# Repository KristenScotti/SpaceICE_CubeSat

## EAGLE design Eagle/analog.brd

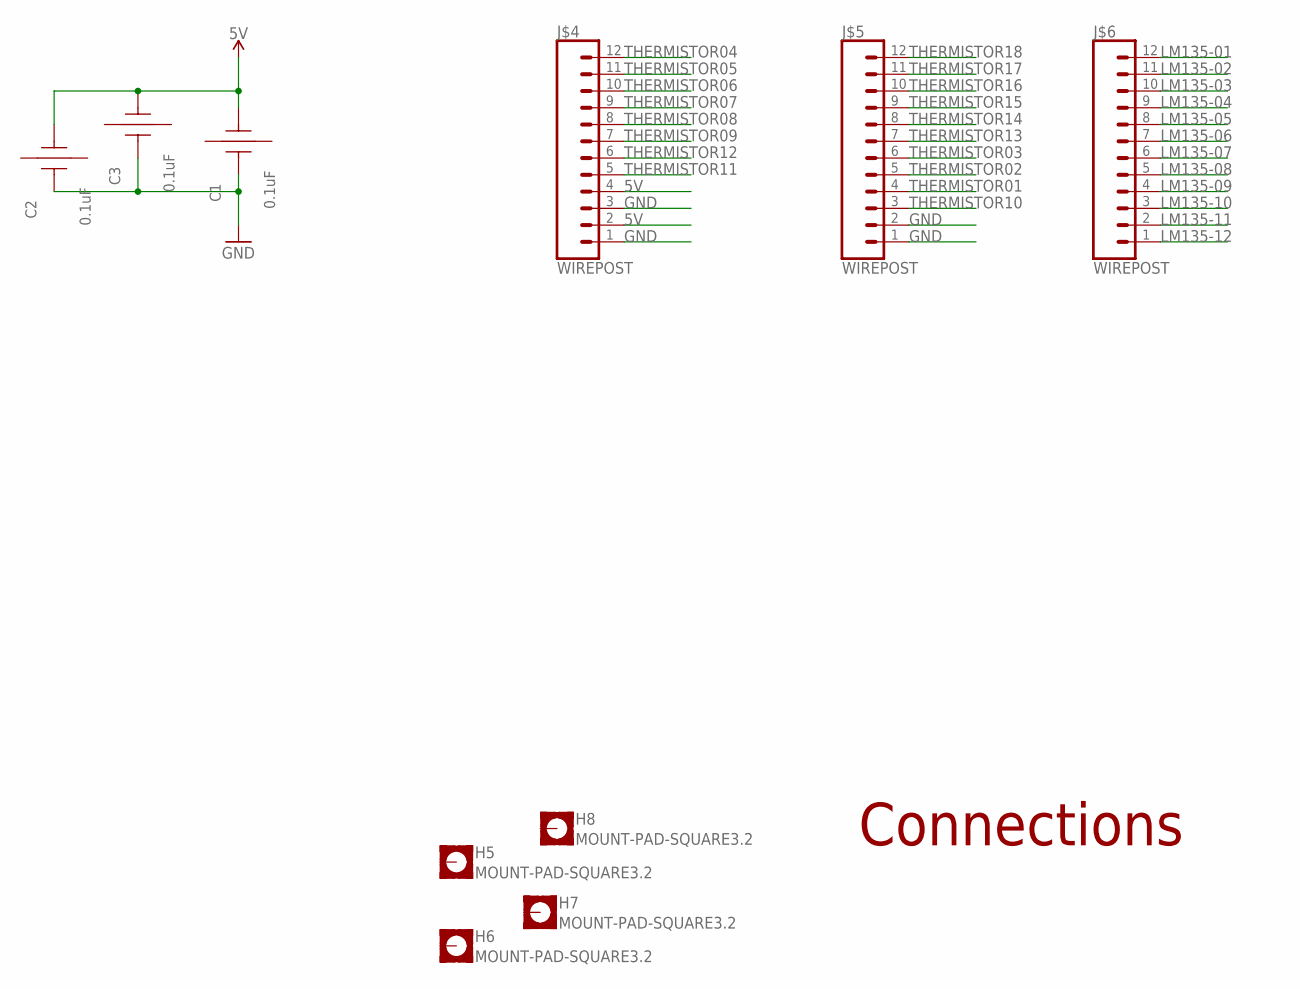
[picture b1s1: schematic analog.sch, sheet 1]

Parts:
C1, C2, C3: 0.1uF; X14
H5, H6, H7, H8: MOUNT-PAD-SQUARE3.2; 3,2-PAD-SQUARE
J$4, J$5, J$6: WIREPOST; WIREWRAPPOST

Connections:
5V: C1.2 (22), C2.2 (22), C3.2 (22), J$4.2, J$4.4; also elsewhere on the board
GND: C1.1 (11), C2.1 (11), C3.1 (11), J$4.1, J$4.3, J$5.1, J$5.2; also elsewhere on the board
LM135-01: J$6.12; also elsewhere on the board
LM135-02: J$6.11; also elsewhere on the board
LM135-03: J$6.10; also elsewhere on the board
LM135-04: J$6.9; also elsewhere on the board
LM135-05: J$6.8; also elsewhere on the board
LM135-06: J$6.7; also elsewhere on the board
LM135-07: J$6.6; also elsewhere on the board
LM135-08: J$6.5; also elsewhere on the board
LM135-09: J$6.4; also elsewhere on the board
LM135-10: J$6.3; also elsewhere on the board
LM135-11: J$6.2; also elsewhere on the board
LM135-12: J$6.1; also elsewhere on the board
THERMISTOR01: J$5.4; also elsewhere on the board
THERMISTOR02: J$5.5; also elsewhere on the board
THERMISTOR03: J$5.6; also elsewhere on the board
THERMISTOR04: J$4.12; also elsewhere on the board
THERMISTOR05: J$4.11; also elsewhere on the board
THERMISTOR06: J$4.10; also elsewhere on the board
THERMISTOR07: J$4.9; also elsewhere on the board
THERMISTOR08: J$4.8; also elsewhere on the board
THERMISTOR09: J$4.7; also elsewhere on the board
THERMISTOR10: J$5.3; also elsewhere on the board
THERMISTOR11: J$4.5; also elsewhere on the board
THERMISTOR12: J$4.6; also elsewhere on the board
THERMISTOR13: J$5.7; also elsewhere on the board
THERMISTOR14: J$5.8; also elsewhere on the board
THERMISTOR15: J$5.9; also elsewhere on the board
THERMISTOR16: J$5.10; also elsewhere on the board
THERMISTOR17: J$5.11; also elsewhere on the board
THERMISTOR18: J$5.12; also elsewhere on the board

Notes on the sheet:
Connections

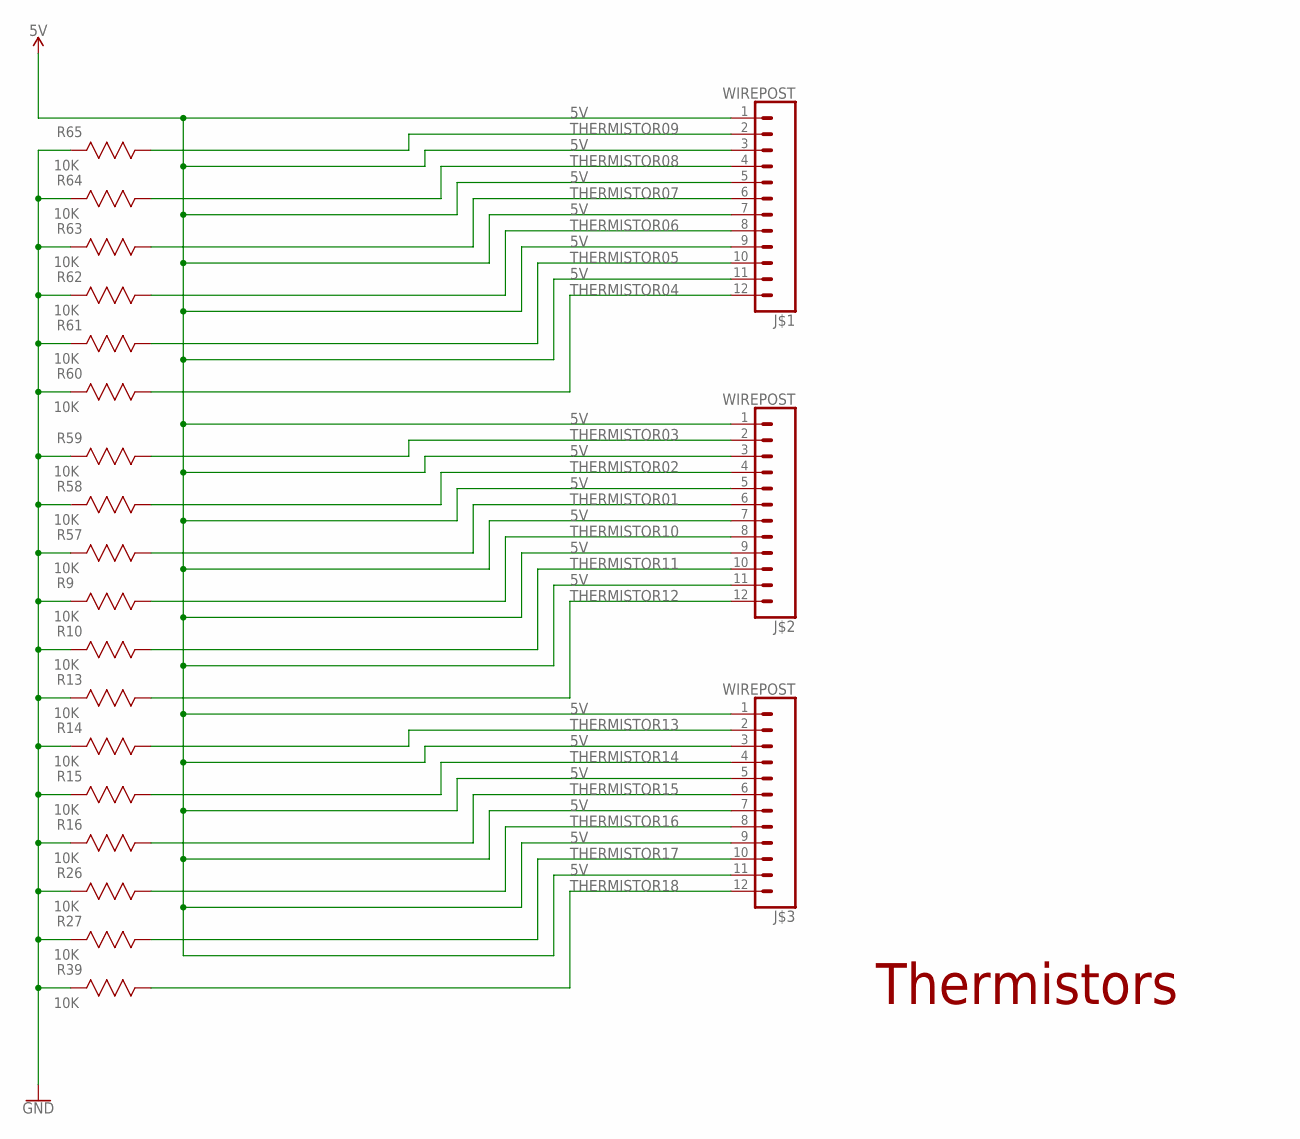
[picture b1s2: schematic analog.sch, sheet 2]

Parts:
J$1, J$2, J$3: WIREPOST; WIREWRAPPOST
R9, R10, R13, R14, R15, R16, R26, R27, R39, R57, R58, R59, R60, R61, R62, R63, R64, R65: 10K; RC0603N

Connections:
5V: J$1.1, J$1.3, J$1.5, J$1.7, J$1.9, J$1.11, J$2.1, J$2.3, J$2.5, J$2.7, J$2.9, J$2.11, J$3.1, J$3.3, J$3.5, J$3.7, J$3.9, J$3.11; also elsewhere on the board
GND: R9.2 (22), R10.2 (22), R13.2 (22), R14.2 (22), R15.2 (22), R16.2 (22), R26.2 (22), R27.2 (22), R39.2 (22), R57.2 (22), R58.2 (22), R59.2 (22), R60.2 (22), R61.2 (22), R62.2 (22), R63.2 (22), R64.2 (22), R65.2 (22); also elsewhere on the board
THERMISTOR01: J$2.6, R57.1 (11); also elsewhere on the board
THERMISTOR02: J$2.4, R58.1 (11); also elsewhere on the board
THERMISTOR03: J$2.2, R59.1 (11); also elsewhere on the board
THERMISTOR04: J$1.12, R60.1 (11); also elsewhere on the board
THERMISTOR05: J$1.10, R61.1 (11); also elsewhere on the board
THERMISTOR06: J$1.8, R62.1 (11); also elsewhere on the board
THERMISTOR07: J$1.6, R63.1 (11); also elsewhere on the board
THERMISTOR08: J$1.4, R64.1 (11); also elsewhere on the board
THERMISTOR09: J$1.2, R65.1 (11); also elsewhere on the board
THERMISTOR10: J$2.8, R9.1 (11); also elsewhere on the board
THERMISTOR11: J$2.10, R10.1 (11); also elsewhere on the board
THERMISTOR12: J$2.12, R13.1 (11); also elsewhere on the board
THERMISTOR13: J$3.2, R14.1 (11); also elsewhere on the board
THERMISTOR14: J$3.4, R15.1 (11); also elsewhere on the board
THERMISTOR15: J$3.6, R16.1 (11); also elsewhere on the board
THERMISTOR16: J$3.8, R26.1 (11); also elsewhere on the board
THERMISTOR17: J$3.10, R27.1 (11); also elsewhere on the board
THERMISTOR18: J$3.12, R39.1 (11); also elsewhere on the board

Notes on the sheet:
Thermistors

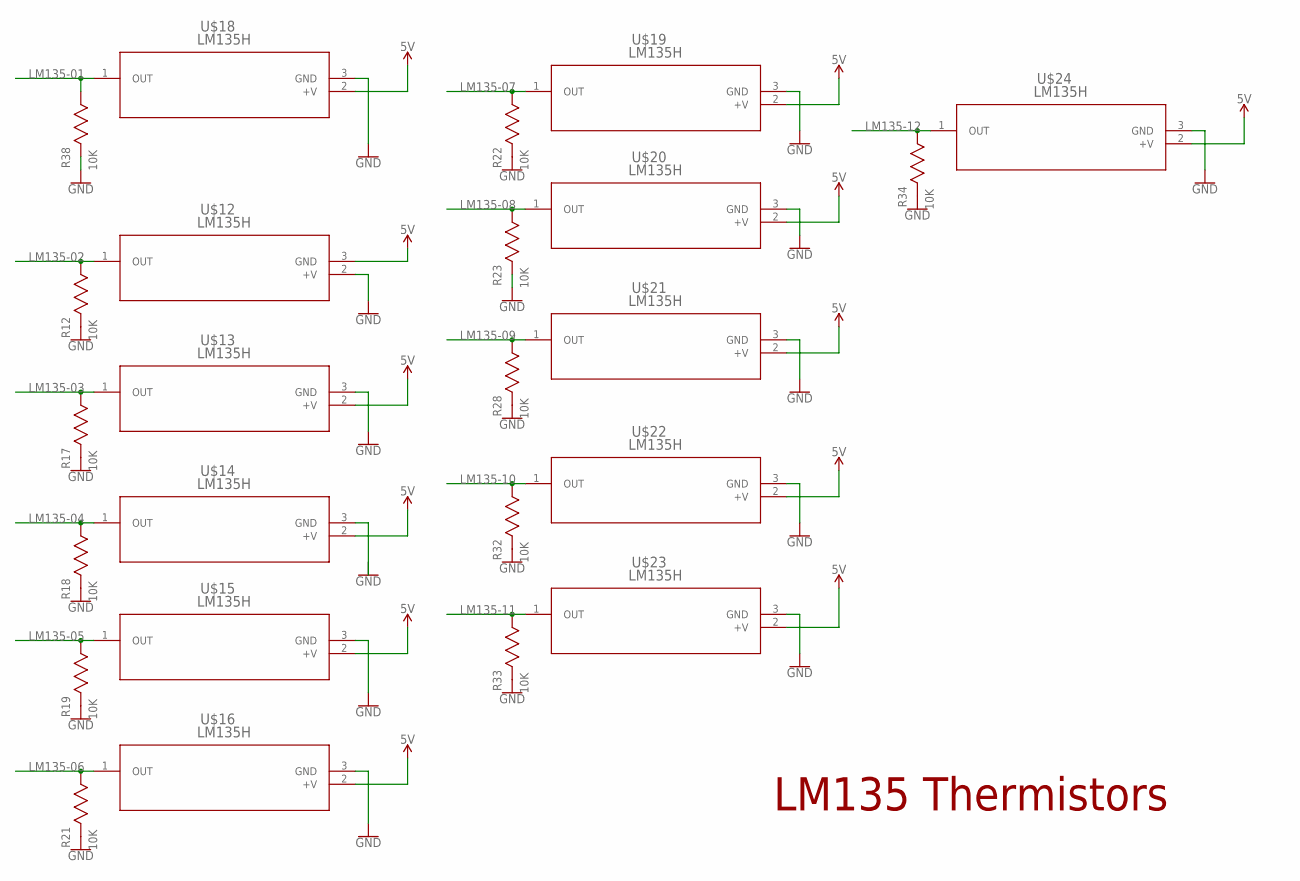
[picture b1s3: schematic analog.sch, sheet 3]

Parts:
R12, R17, R18, R19, R21, R22, R23, R28, R32, R33, R34, R38: 10K; RC0603N
U$12, U$13, U$14, U$15, U$16, U$18, U$19, U$20, U$21, U$22, U$23, U$24: LM135H; TO46

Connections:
5V: U$12.3 (GND), U$13.2 (+V), U$14.2 (+V), U$15.2 (+V), U$16.2 (+V), U$18.2 (+V), U$19.2 (+V), U$20.2 (+V), U$21.2 (+V), U$22.2 (+V), U$23.2 (+V), U$24.2 (+V); also elsewhere on the board
GND: R12.2 (22), R17.2 (22), R18.2 (22), R19.2 (22), R21.2 (22), R22.2 (22), R23.2 (22), R28.2 (22), R32.2 (22), R33.2 (22), R34.2 (22), R38.2 (22), U$12.2 (+V), U$13.3 (GND), U$14.3 (GND), U$15.3 (GND), U$16.3 (GND), U$18.3 (GND), U$19.3 (GND), U$20.3 (GND), U$21.3 (GND), U$22.3 (GND), U$23.3 (GND), U$24.3 (GND); also elsewhere on the board
LM135-01: R38.1 (11), U$18.1 (OUT); also elsewhere on the board
LM135-02: R12.1 (11), U$12.1 (OUT); also elsewhere on the board
LM135-03: R17.1 (11), U$13.1 (OUT); also elsewhere on the board
LM135-04: R18.1 (11), U$14.1 (OUT); also elsewhere on the board
LM135-05: R19.1 (11), U$15.1 (OUT); also elsewhere on the board
LM135-06: R21.1 (11), U$16.1 (OUT); also elsewhere on the board
LM135-07: R22.1 (11), U$19.1 (OUT); also elsewhere on the board
LM135-08: R23.1 (11), U$20.1 (OUT); also elsewhere on the board
LM135-09: R28.1 (11), U$21.1 (OUT); also elsewhere on the board
LM135-10: R32.1 (11), U$22.1 (OUT); also elsewhere on the board
LM135-11: R33.1 (11), U$23.1 (OUT); also elsewhere on the board
LM135-12: R34.1 (11), U$24.1 (OUT); also elsewhere on the board

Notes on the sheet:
LM135 Thermistors

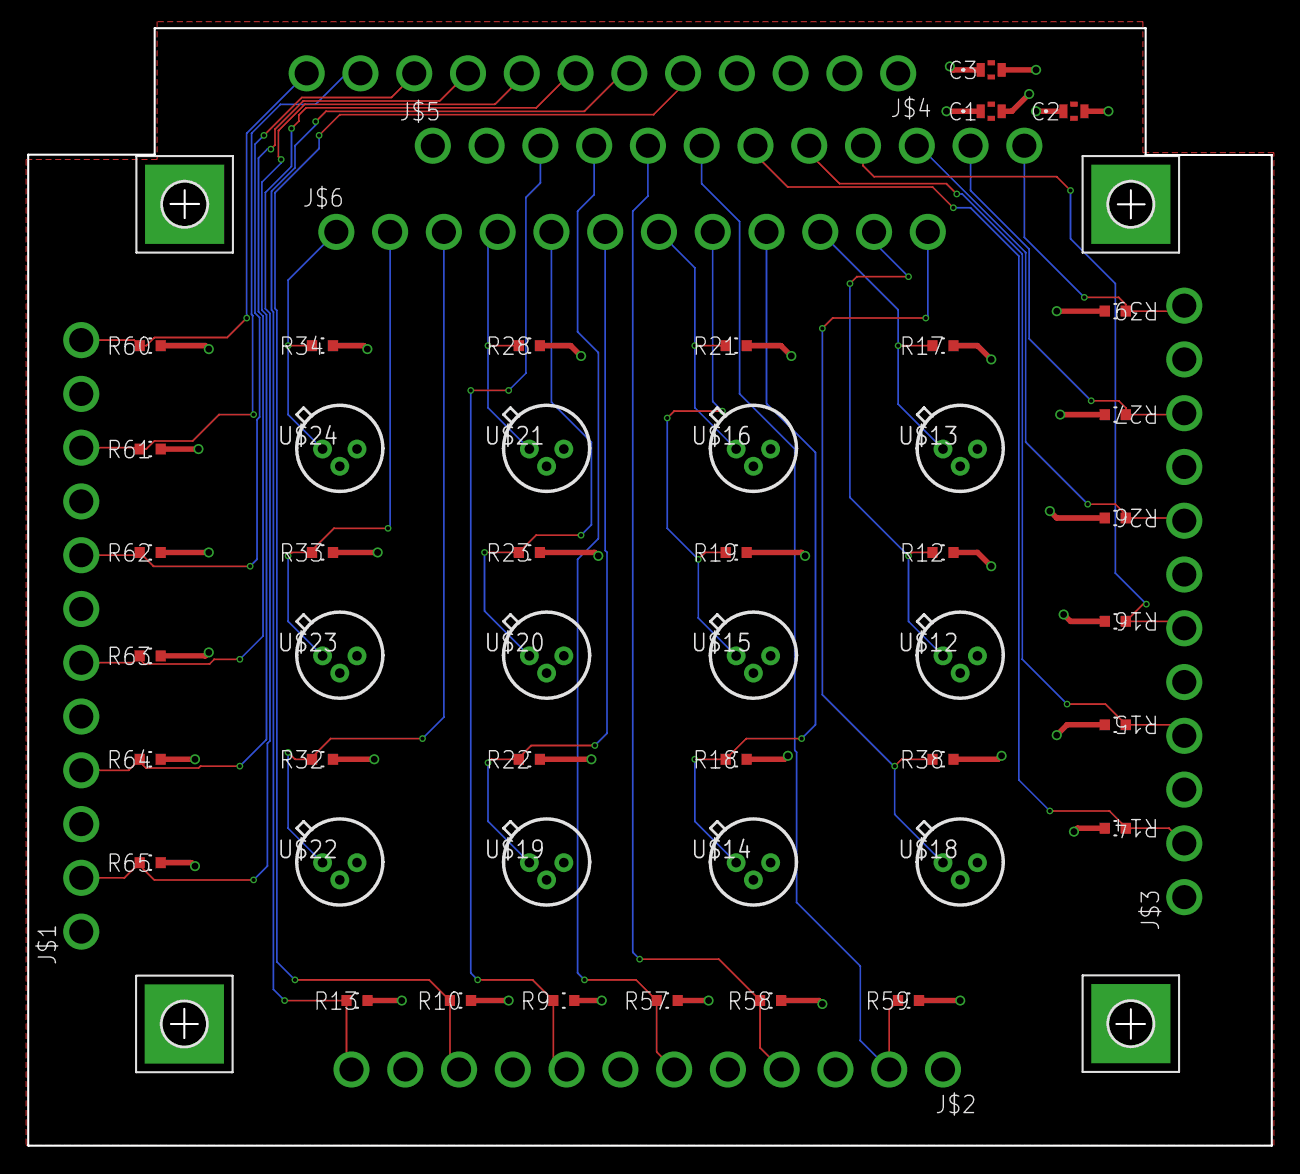
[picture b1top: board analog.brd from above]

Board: 4 copper layers, 91.6 x 82.3 mm, 55 parts (0 on the bottom side), 32 nets.

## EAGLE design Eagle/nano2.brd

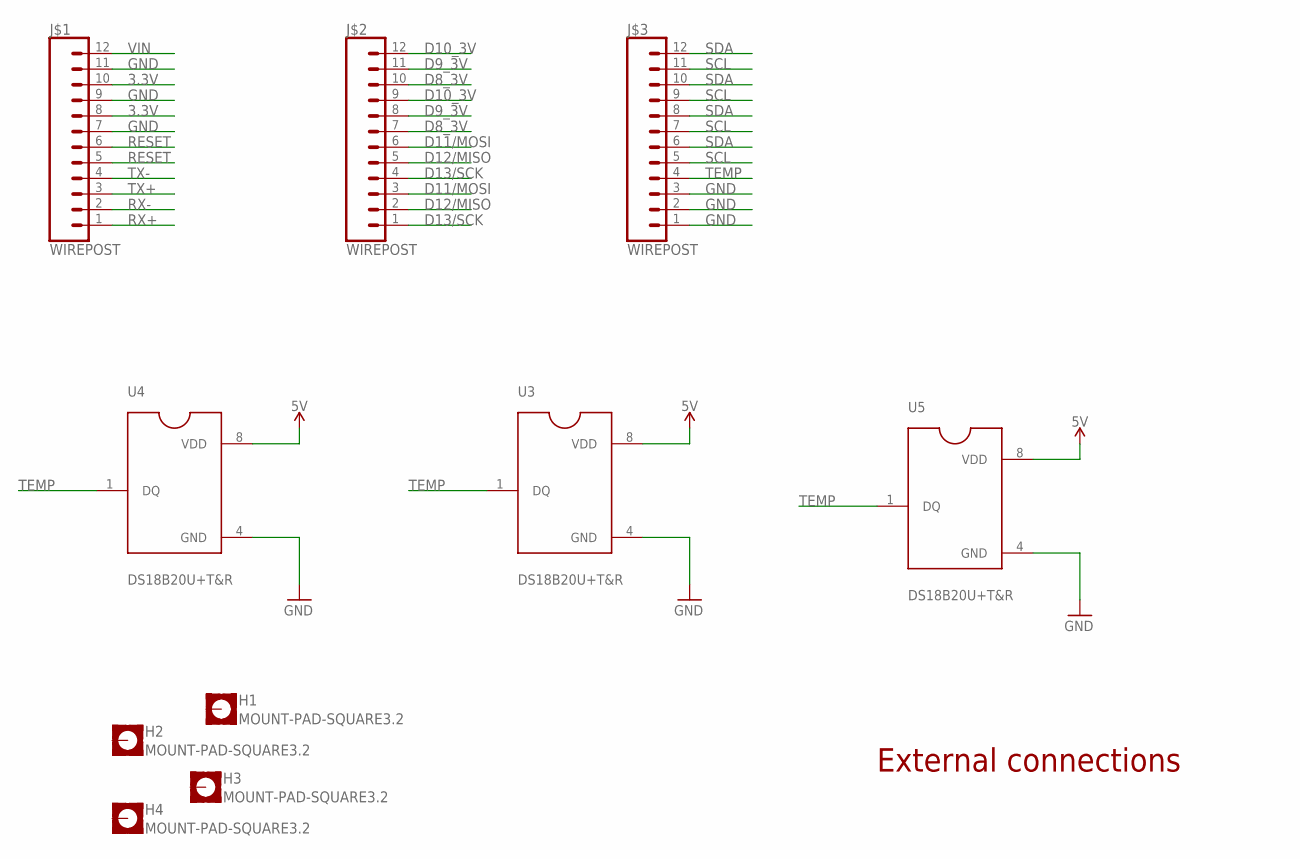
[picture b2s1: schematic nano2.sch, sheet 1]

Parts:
H1, H2, H3, H4: MOUNT-PAD-SQUARE3.2; 3,2-PAD-SQUARE
J$1, J$2, J$3: WIREPOST; WIREWRAPPOST
U3, U4, U5: DS18B20U+T&R; SOP65P500X110-8N

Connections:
3.3V: J$1.8, J$1.10; also elsewhere on the board
5V: U3.8 (VDD), U4.8 (VDD), U5.8 (VDD); also elsewhere on the board
D8_3V: J$2.7, J$2.10; also elsewhere on the board
D9_3V: J$2.8, J$2.11; also elsewhere on the board
D10_3V: J$2.9, J$2.12; also elsewhere on the board
D11/MOSI: J$2.3, J$2.6; also elsewhere on the board
D12/MISO: J$2.2, J$2.5; also elsewhere on the board
D13/SCK: J$2.1, J$2.4; also elsewhere on the board
GND: J$1.7, J$1.9, J$1.11, J$3.1, J$3.2, J$3.3, U3.4 (GND), U4.4 (GND), U5.4 (GND); also elsewhere on the board
RESET: J$1.5, J$1.6; also elsewhere on the board
RX+: J$1.1; also elsewhere on the board
RX-: J$1.2; also elsewhere on the board
SCL: J$3.5, J$3.7, J$3.9, J$3.11; also elsewhere on the board
SDA: J$3.6, J$3.8, J$3.10, J$3.12; also elsewhere on the board
TEMP: J$3.4, U3.1 (DQ), U4.1 (DQ), U5.1 (DQ)
TX+: J$1.3; also elsewhere on the board
TX-: J$1.4; also elsewhere on the board
VIN: J$1.12; also elsewhere on the board

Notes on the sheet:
External connections

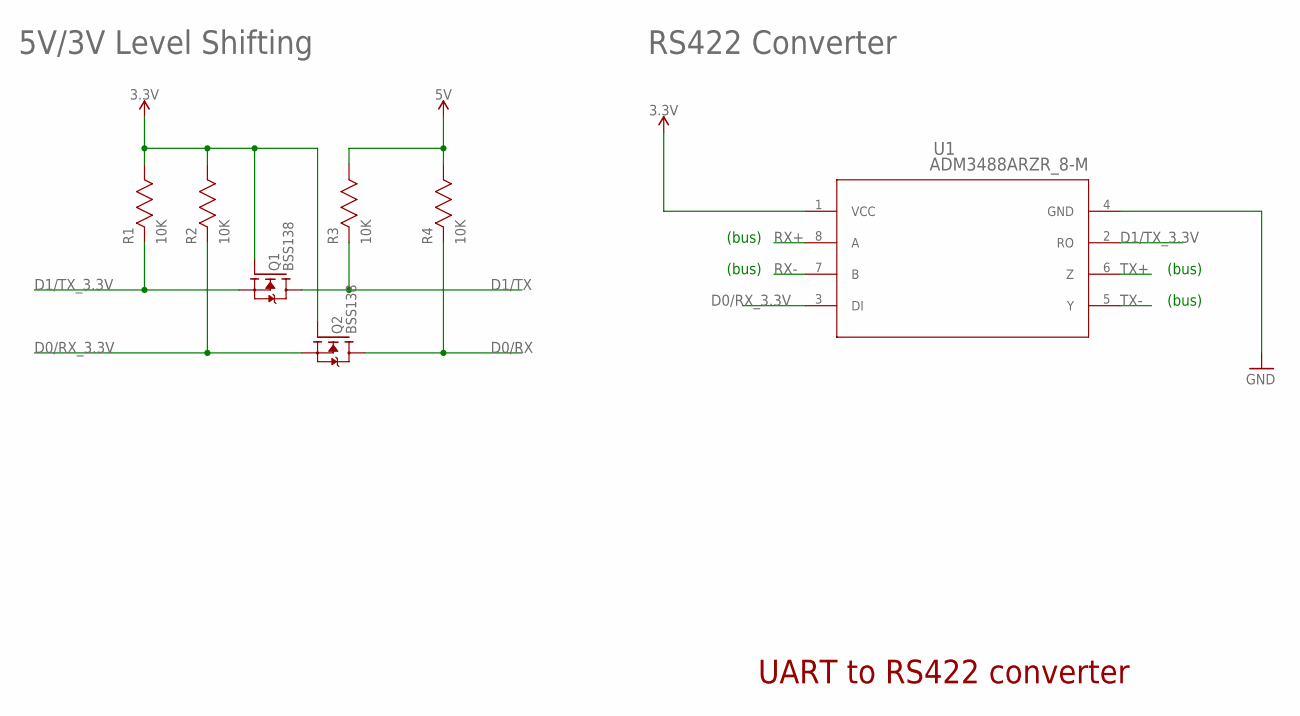
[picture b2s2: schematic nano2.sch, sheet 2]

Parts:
Q1, Q2: BSS138; SOT-23
R1, R2, R3, R4: 10K; RC0603N
U1: ADM3488ARZR_8-M; R_8-M

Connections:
3.3V: Q1.G, Q2.G, R1.1 (11), R2.1 (11), U1.1 (VCC); also elsewhere on the board
5V: R3.1 (11), R4.1 (11); also elsewhere on the board
D0/RX: Q2.D, R4.2 (22); also elsewhere on the board
D0/RX_3.3V: Q2.S, R2.2 (22), U1.3 (DI)
D1/TX: Q1.D, R3.2 (22); also elsewhere on the board
D1/TX_3.3V: Q1.S, R1.2 (22), U1.2 (RO)
GND: U1.4 (GND); also elsewhere on the board
RX+: U1.8 (A); also elsewhere on the board
RX-: U1.7 (B); also elsewhere on the board
TX+: U1.6 (Z); also elsewhere on the board
TX-: U1.5 (Y); also elsewhere on the board

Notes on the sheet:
5V/3V Level Shifting
UART to RS422 converter
(bus)
RS422 Converter

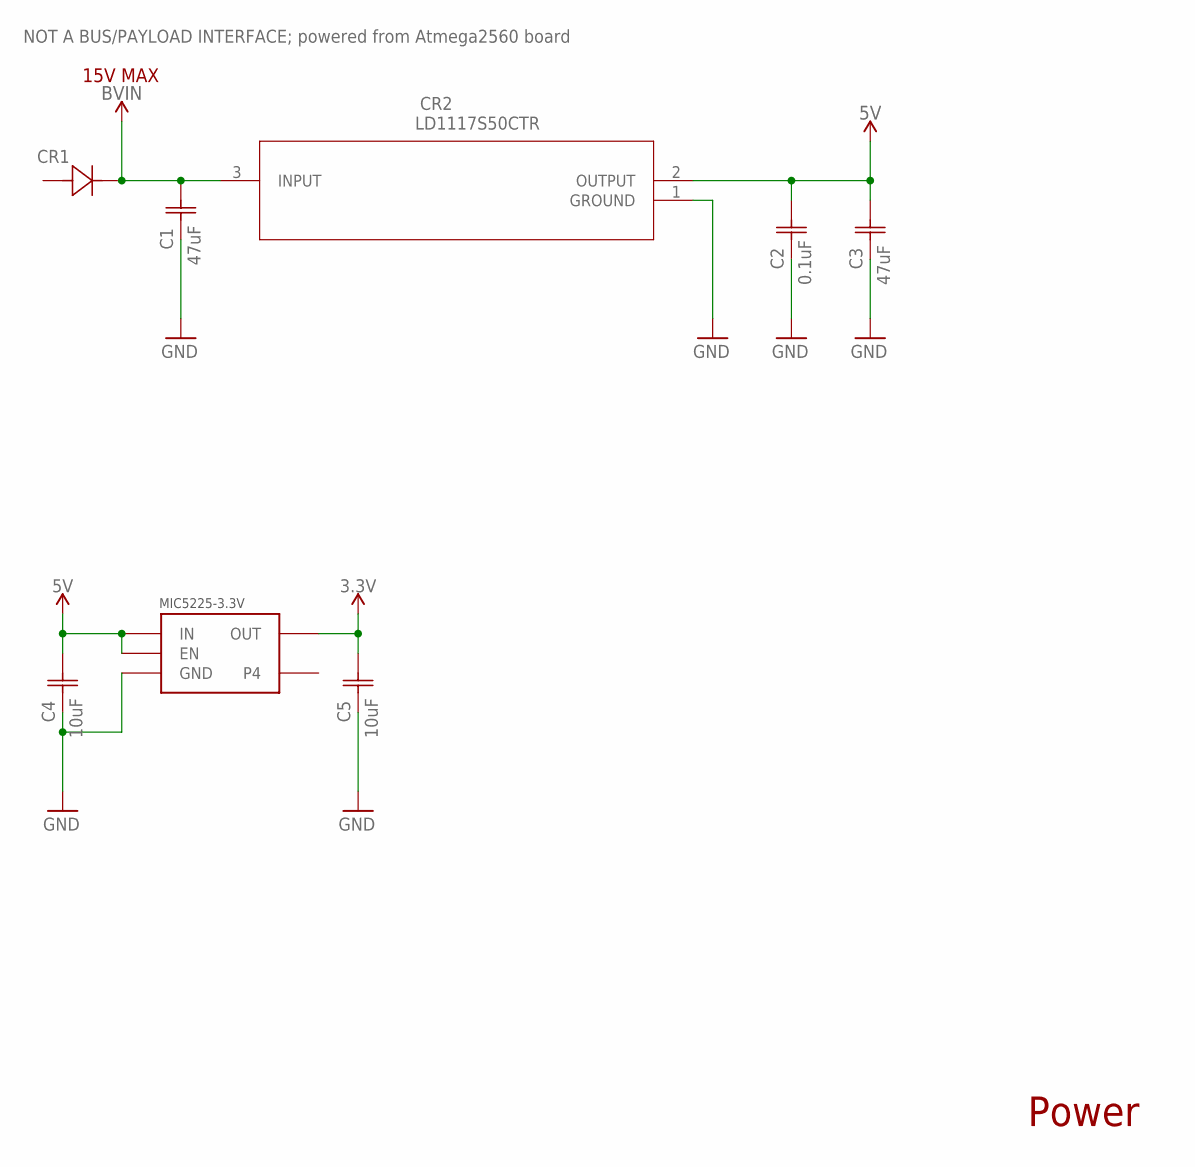
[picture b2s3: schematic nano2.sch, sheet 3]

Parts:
C1, C3: 47uF; CAP_5750
C2: 0.1uF; CAP_01
C4, C5: 10uF; CAP_GRM219R61A106KE44D
CR1: DIODE_600V_3A
CR2: LD1117S50CTR; SOT-223
U2: MIC5225-3.3V; SOT23-5

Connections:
3.3V: C5.2, U2.OUT; also elsewhere on the board
5V: C2.2, C3.2, C4.2, CR2.2 (OUTPUT), U2.EN, U2.IN; also elsewhere on the board
GND: C1.1, C2.1, C3.1, C4.1, C5.1, CR2.1 (GROUND), U2.GND; also elsewhere on the board
VIN: C1.2, CR1.1 (12), CR2.3 (INPUT); also elsewhere on the board

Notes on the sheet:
Power
15V MAX
NOT A BUS/PAYLOAD INTERFACE; powered from Atmega2560 board

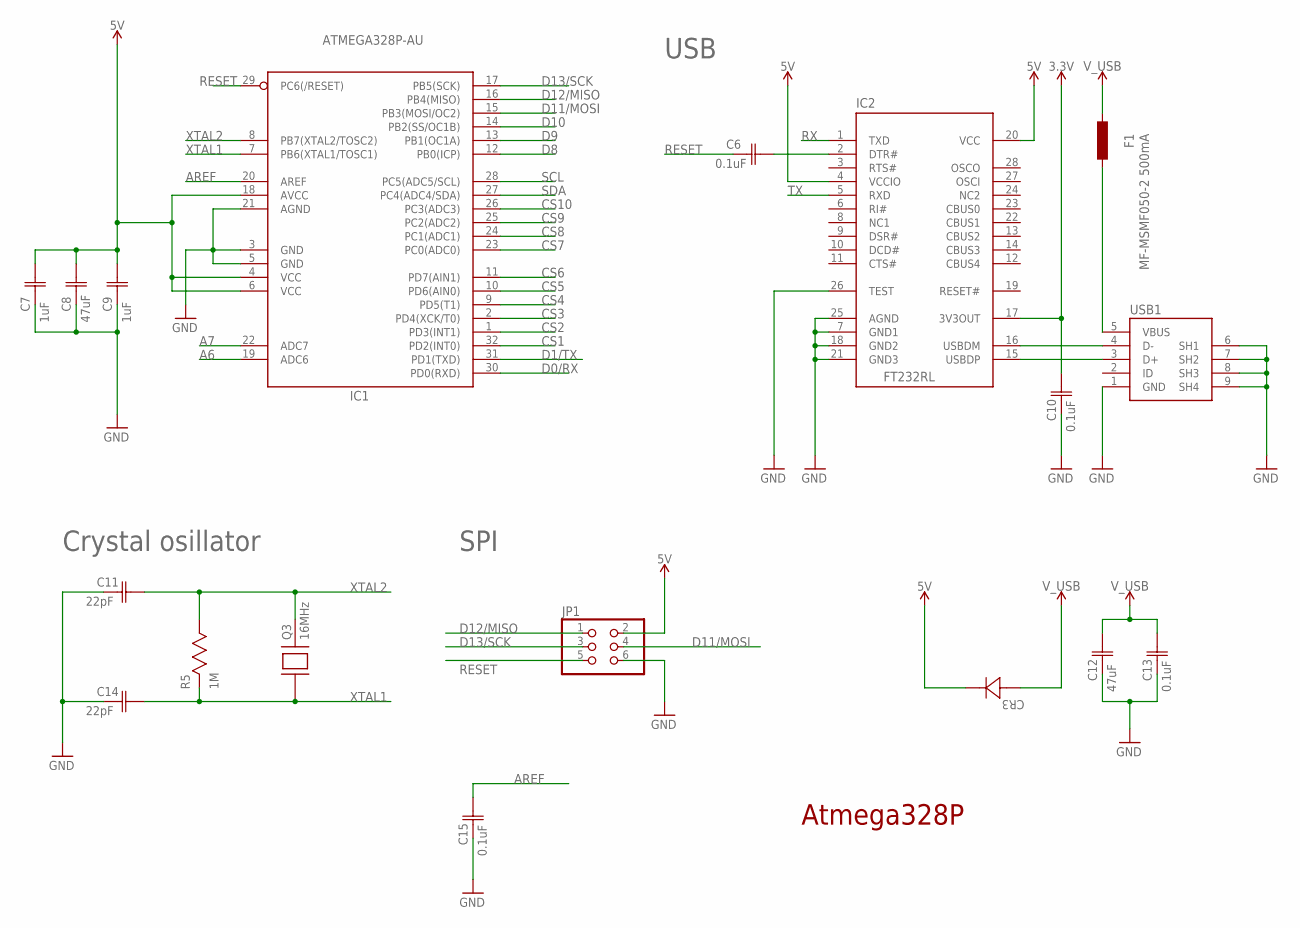
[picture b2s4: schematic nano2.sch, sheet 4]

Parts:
C6, C10, C13, C15: 0.1uF; CAP_01
C7, C9: 1uF; YAG_CC0805
C8, C12: 47uF; CAP_5750
C11, C14: 22pF; CC0805N
CR3: DIODE_600V_3A
F1: MF-MSMF050-2 500mA; L1812
IC1: ATMEGA328P-AU; TQFP32-08
IC2: FT232RL; SSOP28
JP1: 0114_PH254-203DF118A00V; 2X03
Q3: 16MHz; OSCILLATOR
R5: 1M; RC0603N
USB1: 0219_14850; USB-MINI-B_2

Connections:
3.3V: C10.2, IC2.17 (3V3OUT); also elsewhere on the board
5V: C7.2, C8.2, C9.2, CR3.1 (12), IC1.4 (VCC), IC1.6 (VCC), IC1.18 (AVCC), IC2.4 (VCCIO), IC2.20 (VCC), JP1.2; also elsewhere on the board
A6: IC1.19 (ADC6)
A7: IC1.22 (ADC7)
AREF: C15.2, IC1.20 (AREF)
CS1: IC1.32 (PD2(INT0)); also elsewhere on the board
CS2: IC1.1 (PD3(INT1)); also elsewhere on the board
CS3: IC1.2 (PD4(XCK/T0)); also elsewhere on the board
CS4: IC1.9 (PD5(T1)); also elsewhere on the board
CS5: IC1.10 (PD6(AIN0)); also elsewhere on the board
CS6: IC1.11 (PD7(AIN1)); also elsewhere on the board
CS7: IC1.23 (PC0(ADC0)); also elsewhere on the board
CS8: IC1.24 (PC1(ADC1)); also elsewhere on the board
CS9: IC1.25 (PC2(ADC2)); also elsewhere on the board
CS10: IC1.26 (PC3(ADC3)); also elsewhere on the board
D0/RX: IC1.30 (PD0(RXD)); also elsewhere on the board
D1/TX: IC1.31 (PD1(TXD)); also elsewhere on the board
D8: IC1.12 (PB0(ICP)); also elsewhere on the board
D9: IC1.13 (PB1(OC1A)); also elsewhere on the board
D10: IC1.14 (PB2(SS/OC1B)); also elsewhere on the board
D11/MOSI: IC1.15 (PB3(MOSI/OC2)), JP1.4; also elsewhere on the board
D12/MISO: IC1.16 (PB4(MISO)), JP1.1; also elsewhere on the board
D13/SCK: IC1.17 (PB5(SCK)), JP1.3; also elsewhere on the board
GND: C7.1, C8.1, C9.1, C10.1, C11.1, C12.1, C13.1, C14.1, C15.1, IC1.3 (GND), IC1.5 (GND), IC1.21 (AGND), IC2.7 (GND1), IC2.18 (GND2), IC2.21 (GND3), IC2.25 (AGND), IC2.26 (TEST), JP1.6, USB1.1 (GND), USB1.6 (SH1), USB1.7 (SH2), USB1.8 (SH3), USB1.9 (SH4); also elsewhere on the board
unnamed: F1.2, USB1.5 (VBUS)
unnamed: C6.2, IC2.2 (DTR#)
unnamed: IC2.15 (USBDP), USB1.3 (D+)
unnamed: IC2.16 (USBDM), USB1.4 (D-)
RESET: C6.1, IC1.29 (PC6(/RESET)), JP1.5; also elsewhere on the board
RX: IC2.1 (TXD)
SCL: IC1.28 (PC5(ADC5/SCL)); also elsewhere on the board
SDA: IC1.27 (PC4(ADC4/SDA)); also elsewhere on the board
TX: IC2.5 (RXD)
V_USB: C12.2, C13.2, CR3.2 (21), F1.1
XTAL1: C14.2, IC1.7 (PB6(XTAL1/TOSC1)), Q3.1, R5.2 (22)
XTAL2: C11.2, IC1.8 (PB7(XTAL2/TOSC2)), Q3.2, R5.1 (11)

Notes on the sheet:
Atmega328P
USB
Crystal osillator
SPI

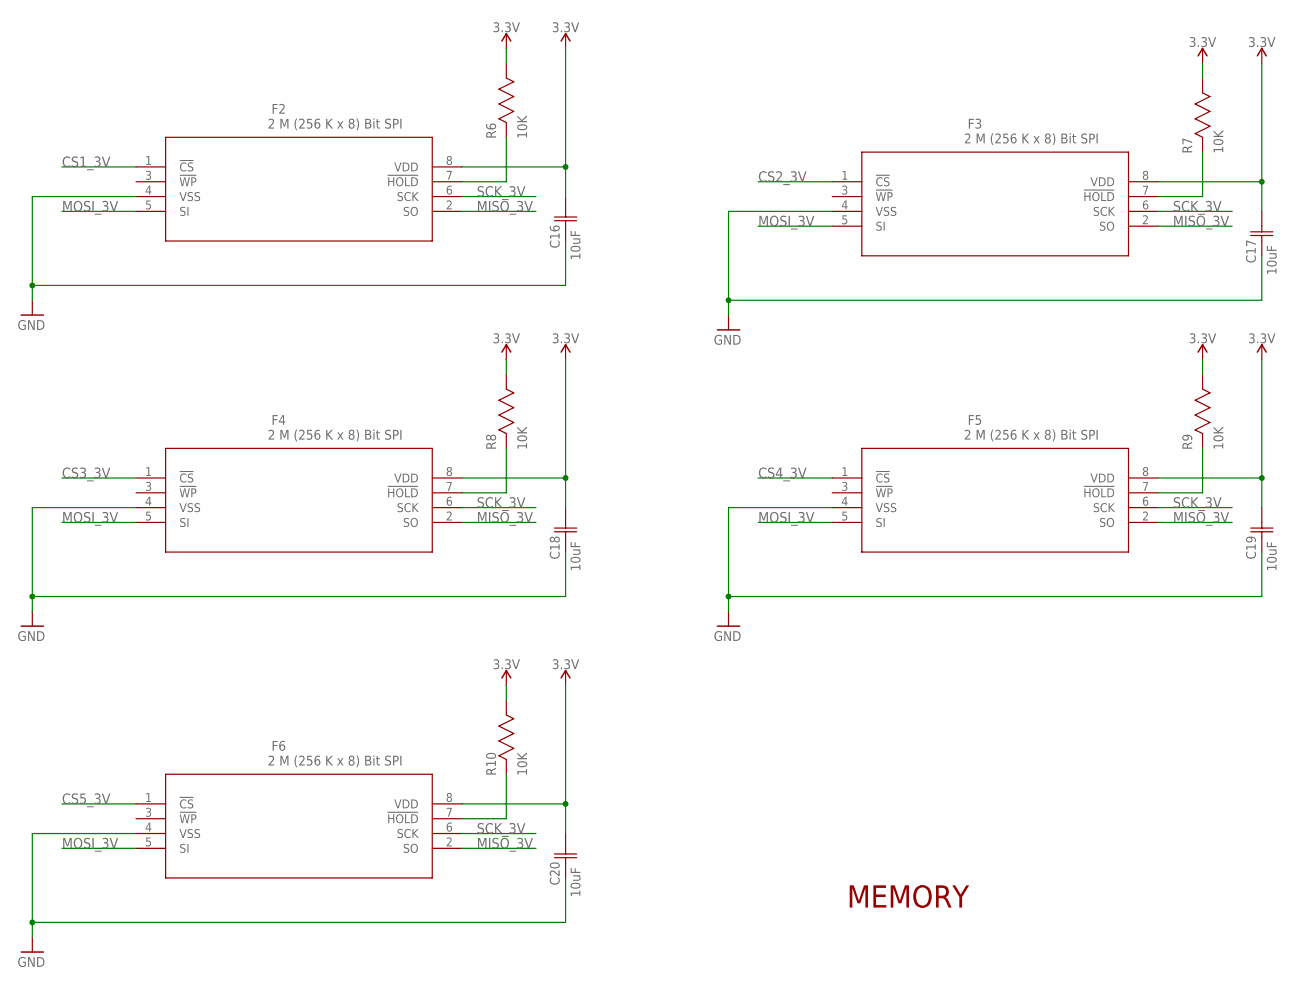
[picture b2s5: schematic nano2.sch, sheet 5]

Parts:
C16, C17, C18, C19, C20: 10uF; CAP_GRM219R61A106KE44D
F2, F3, F4, F5, F6: 2 M (256 K x 8) Bit SPI; FRAM_MB85RS2MTA_FPT-8P-M09
R6, R7, R8, R9, R10: 10K; RC0603N

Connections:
3.3V: C16.2, C17.2, C18.2, C19.2, C20.2, F2.8 (VDD), F3.8 (VDD), F4.8 (VDD), F5.8 (VDD), F6.8 (VDD), R6.1 (11), R7.1 (11), R8.1 (11), R9.1 (11), R10.1 (11); also elsewhere on the board
CS1_3V: F2.1 (!CS); also elsewhere on the board
CS2_3V: F3.1 (!CS); also elsewhere on the board
CS3_3V: F4.1 (!CS); also elsewhere on the board
CS4_3V: F5.1 (!CS); also elsewhere on the board
CS5_3V: F6.1 (!CS); also elsewhere on the board
GND: C16.1, C17.1, C18.1, C19.1, C20.1, F2.4 (VSS), F3.4 (VSS), F4.4 (VSS), F5.4 (VSS), F6.4 (VSS); also elsewhere on the board
MISO_3V: F2.2 (SO), F3.2 (SO), F4.2 (SO), F5.2 (SO), F6.2 (SO); also elsewhere on the board
MOSI_3V: F2.5 (SI), F3.5 (SI), F4.5 (SI), F5.5 (SI), F6.5 (SI); also elsewhere on the board
unnamed: F2.7 (!HOLD), R6.2 (22)
unnamed: F4.7 (!HOLD), R8.2 (22)
unnamed: F6.7 (!HOLD), R10.2 (22)
unnamed: F3.7 (!HOLD), R7.2 (22)
unnamed: F5.7 (!HOLD), R9.2 (22)
SCK_3V: F2.6 (SCK), F3.6 (SCK), F4.6 (SCK), F5.6 (SCK), F6.6 (SCK); also elsewhere on the board

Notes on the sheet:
MEMORY

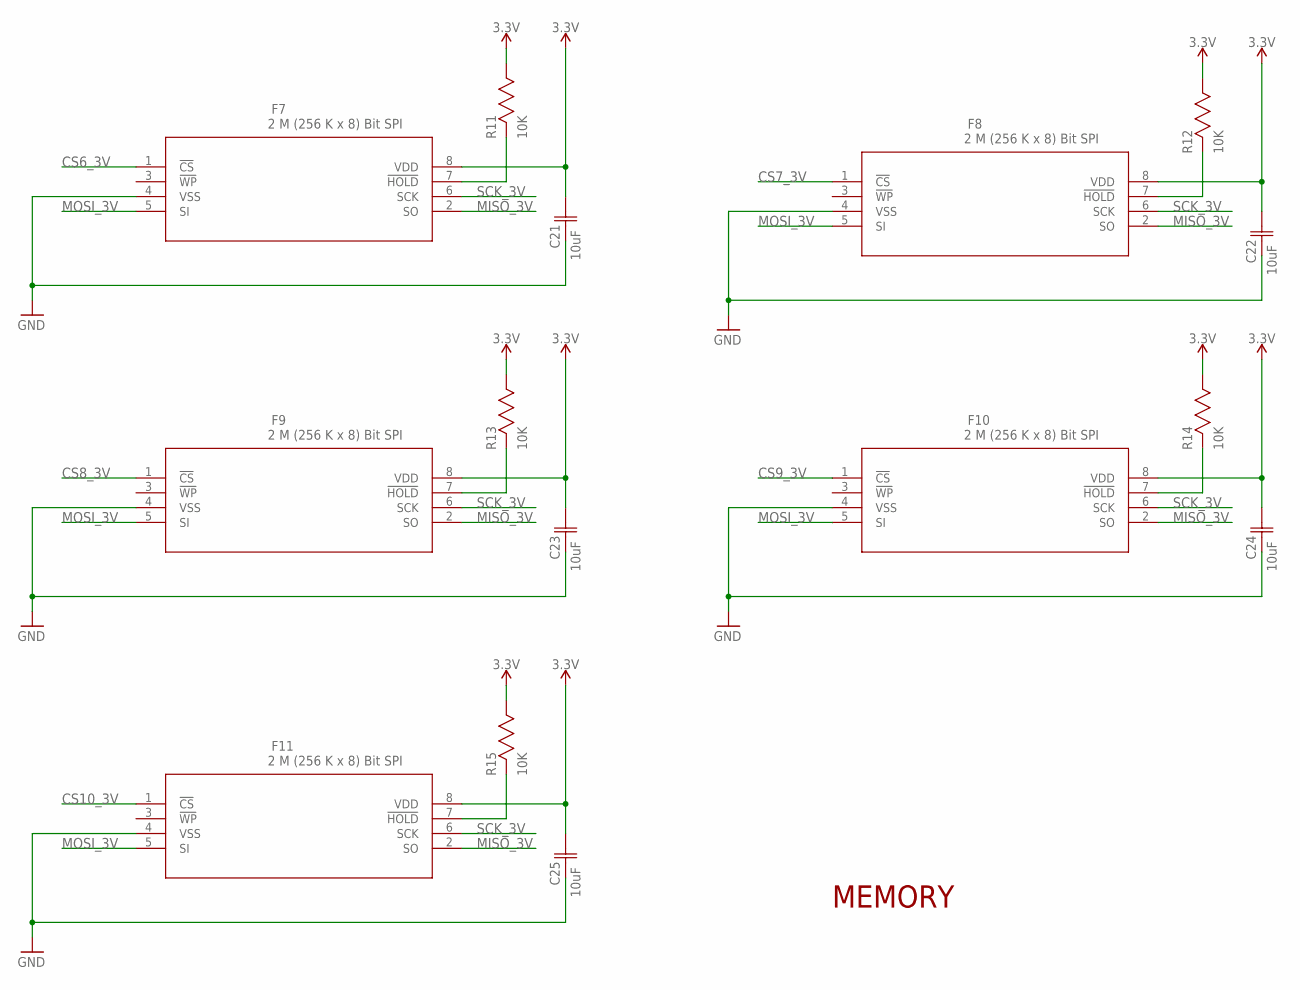
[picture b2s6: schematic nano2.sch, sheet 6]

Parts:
C21, C22, C23, C24, C25: 10uF; CAP_GRM219R61A106KE44D
F7, F8, F9, F10, F11: 2 M (256 K x 8) Bit SPI; FRAM_MB85RS2MTA_FPT-8P-M09
R11, R12, R13, R14, R15: 10K; RC0603N

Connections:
3.3V: C21.2, C22.2, C23.2, C24.2, C25.2, F7.8 (VDD), F8.8 (VDD), F9.8 (VDD), F10.8 (VDD), F11.8 (VDD), R11.1 (11), R12.1 (11), R13.1 (11), R14.1 (11), R15.1 (11); also elsewhere on the board
CS6_3V: F7.1 (!CS); also elsewhere on the board
CS7_3V: F8.1 (!CS); also elsewhere on the board
CS8_3V: F9.1 (!CS); also elsewhere on the board
CS9_3V: F10.1 (!CS); also elsewhere on the board
CS10_3V: F11.1 (!CS); also elsewhere on the board
GND: C21.1, C22.1, C23.1, C24.1, C25.1, F7.4 (VSS), F8.4 (VSS), F9.4 (VSS), F10.4 (VSS), F11.4 (VSS); also elsewhere on the board
MISO_3V: F7.2 (SO), F8.2 (SO), F9.2 (SO), F10.2 (SO), F11.2 (SO); also elsewhere on the board
MOSI_3V: F7.5 (SI), F8.5 (SI), F9.5 (SI), F10.5 (SI), F11.5 (SI); also elsewhere on the board
unnamed: F7.7 (!HOLD), R11.2 (22)
unnamed: F9.7 (!HOLD), R13.2 (22)
unnamed: F11.7 (!HOLD), R15.2 (22)
unnamed: F8.7 (!HOLD), R12.2 (22)
unnamed: F10.7 (!HOLD), R14.2 (22)
SCK_3V: F7.6 (SCK), F8.6 (SCK), F9.6 (SCK), F10.6 (SCK), F11.6 (SCK); also elsewhere on the board

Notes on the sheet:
MEMORY

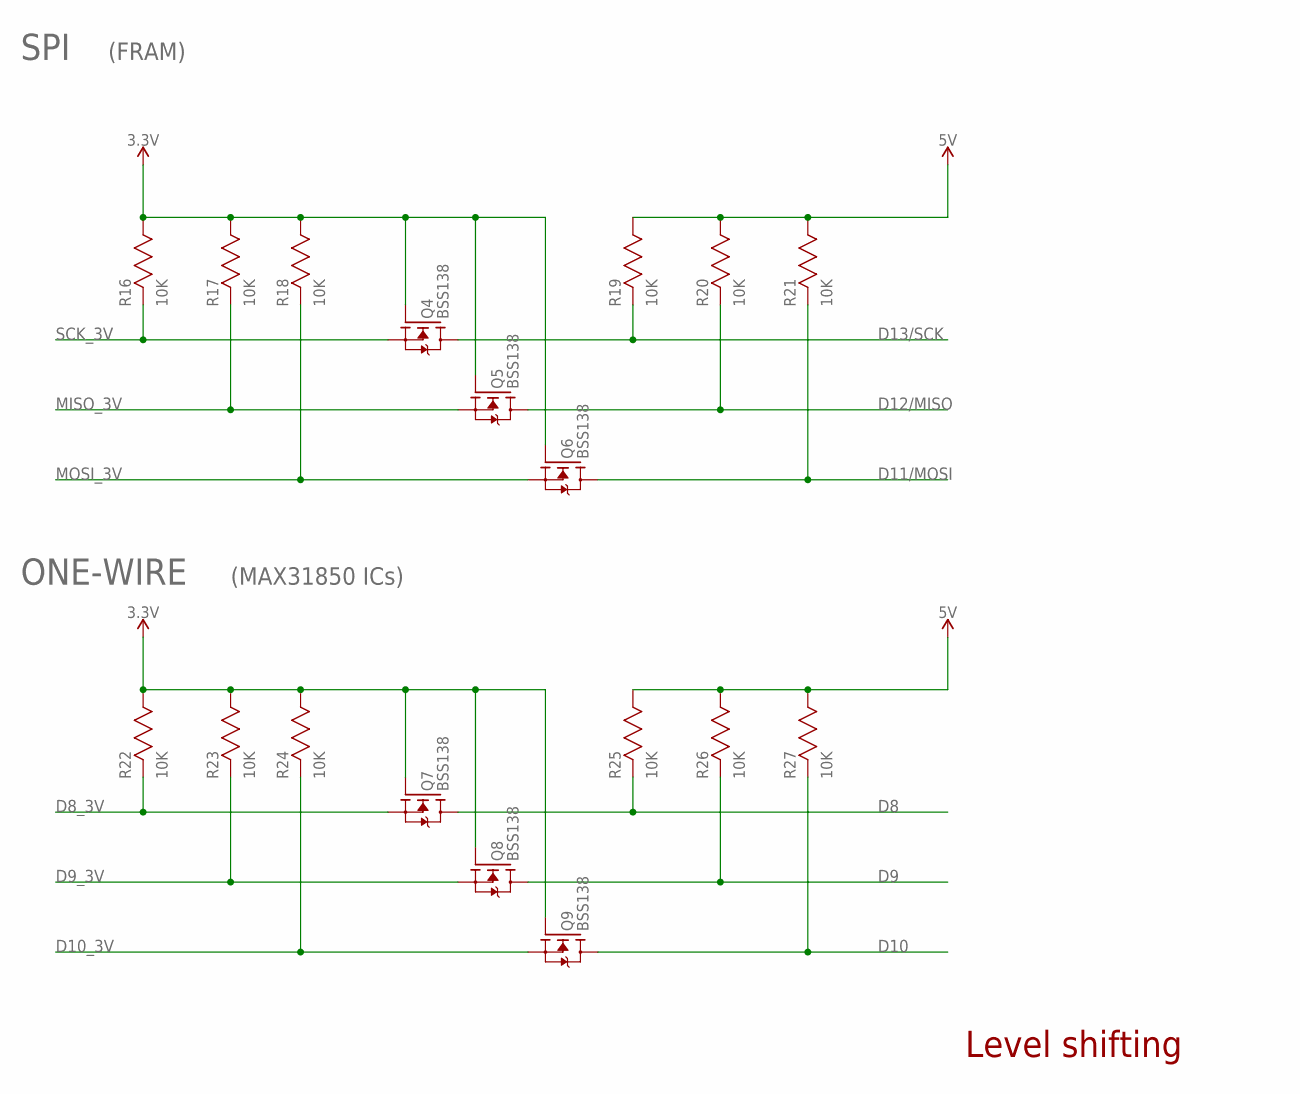
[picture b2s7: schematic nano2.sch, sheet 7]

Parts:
Q4, Q5, Q6, Q7, Q8, Q9: BSS138; SOT-23
R16, R17, R18, R19, R20, R21, R22, R23, R24, R25, R26, R27: 10K; RC0603N

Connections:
3.3V: Q4.G, Q5.G, Q6.G, Q7.G, Q8.G, Q9.G, R16.1 (11), R17.1 (11), R18.1 (11), R22.1 (11), R23.1 (11), R24.1 (11); also elsewhere on the board
5V: R19.1 (11), R20.1 (11), R21.1 (11), R25.1 (11), R26.1 (11), R27.1 (11); also elsewhere on the board
D8: Q7.D, R25.2 (22); also elsewhere on the board
D8_3V: Q7.S, R22.2 (22); also elsewhere on the board
D9: Q8.D, R26.2 (22); also elsewhere on the board
D9_3V: Q8.S, R23.2 (22); also elsewhere on the board
D10: Q9.D, R27.2 (22); also elsewhere on the board
D10_3V: Q9.S, R24.2 (22); also elsewhere on the board
D11/MOSI: Q6.D, R21.2 (22); also elsewhere on the board
D12/MISO: Q5.D, R20.2 (22); also elsewhere on the board
D13/SCK: Q4.D, R19.2 (22); also elsewhere on the board
MISO_3V: Q5.S, R17.2 (22); also elsewhere on the board
MOSI_3V: Q6.S, R18.2 (22); also elsewhere on the board
SCK_3V: Q4.S, R16.2 (22); also elsewhere on the board

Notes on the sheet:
Level shifting
SPI
ONE-WIRE
(MAX31850 ICs)
(FRAM)

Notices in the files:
parts and their libraries:
SparkFun-PowerSymbols: Licensing: Creative Commons ShareAlike 4.0 International - https://creativecommons.org/licenses/by-sa/4.0
microbuilder: This work is placed in the public domain, and may be freely used for commercial and non-commercial work with the following conditions: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
